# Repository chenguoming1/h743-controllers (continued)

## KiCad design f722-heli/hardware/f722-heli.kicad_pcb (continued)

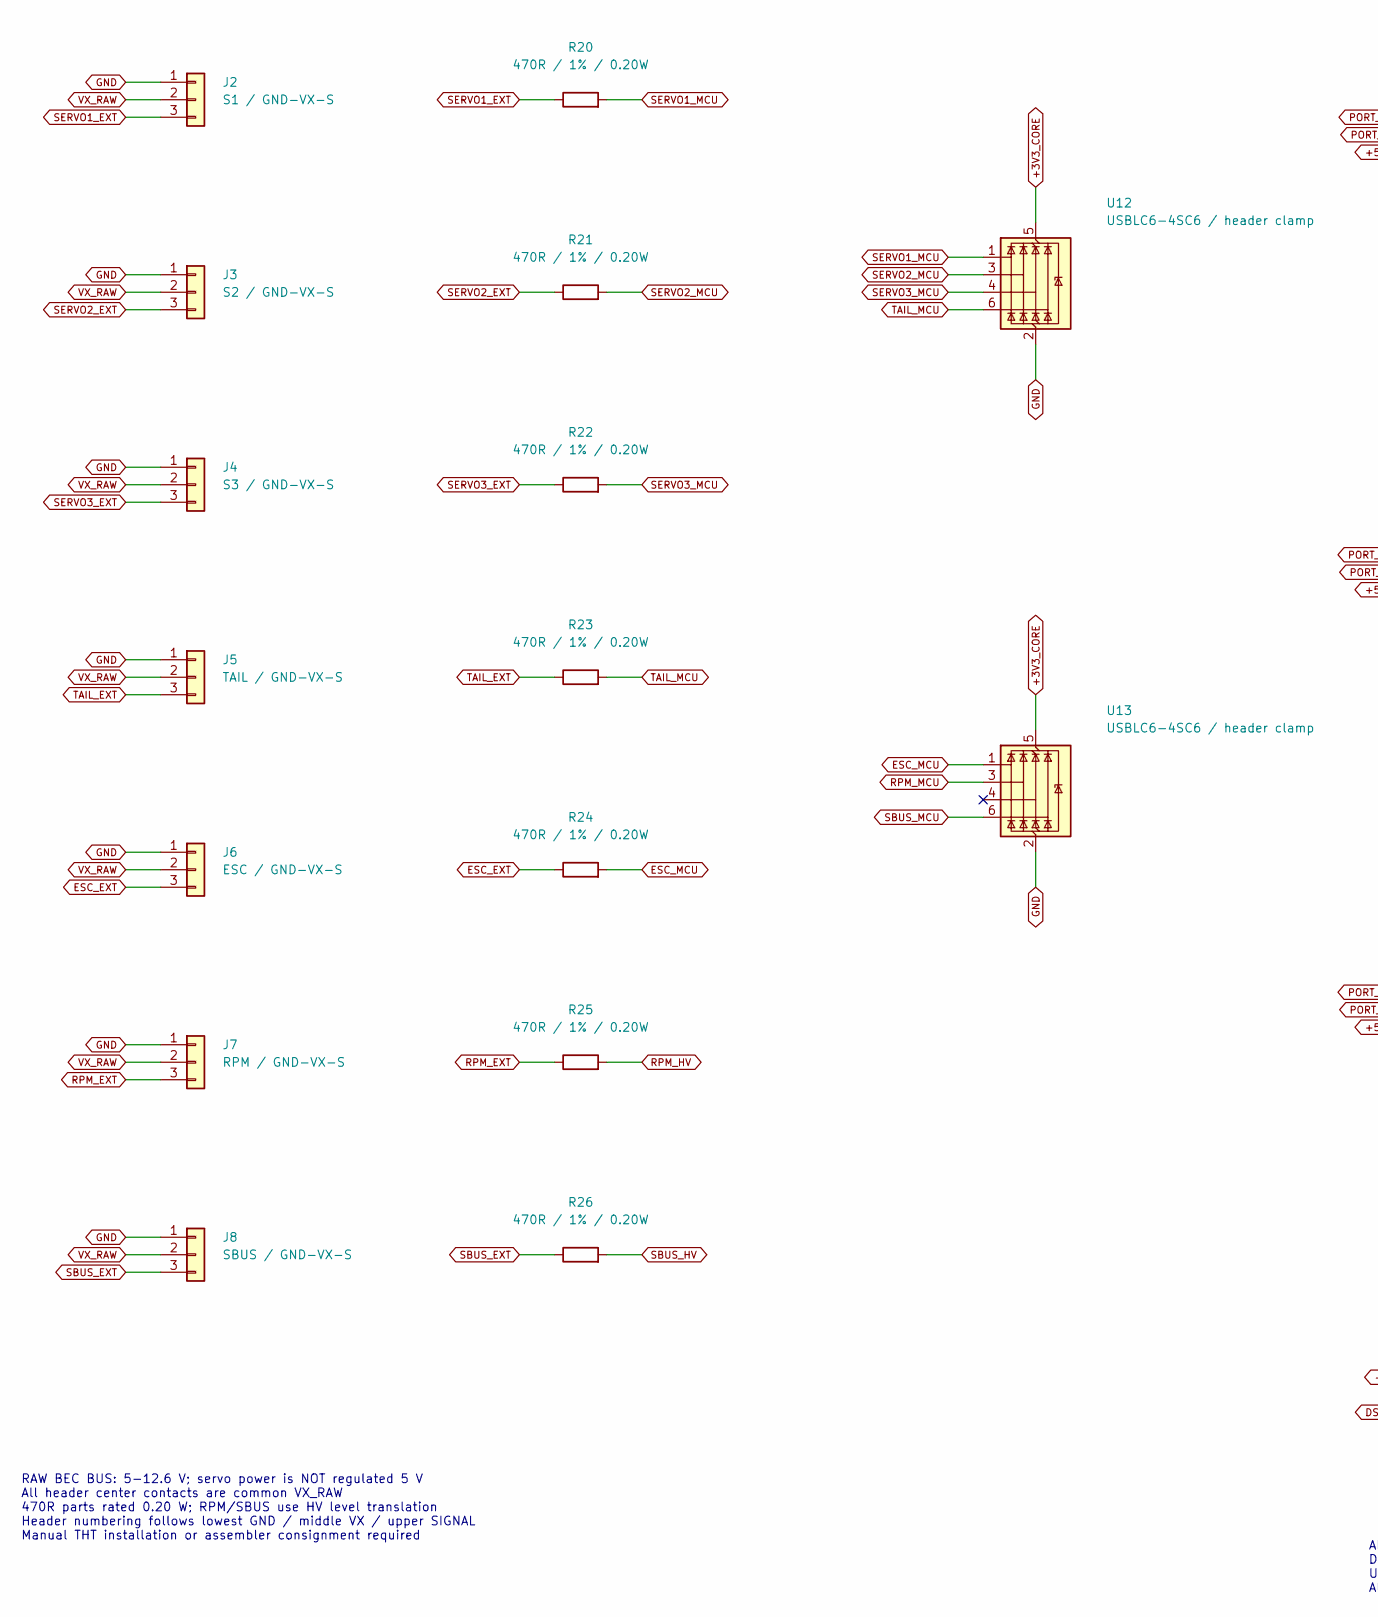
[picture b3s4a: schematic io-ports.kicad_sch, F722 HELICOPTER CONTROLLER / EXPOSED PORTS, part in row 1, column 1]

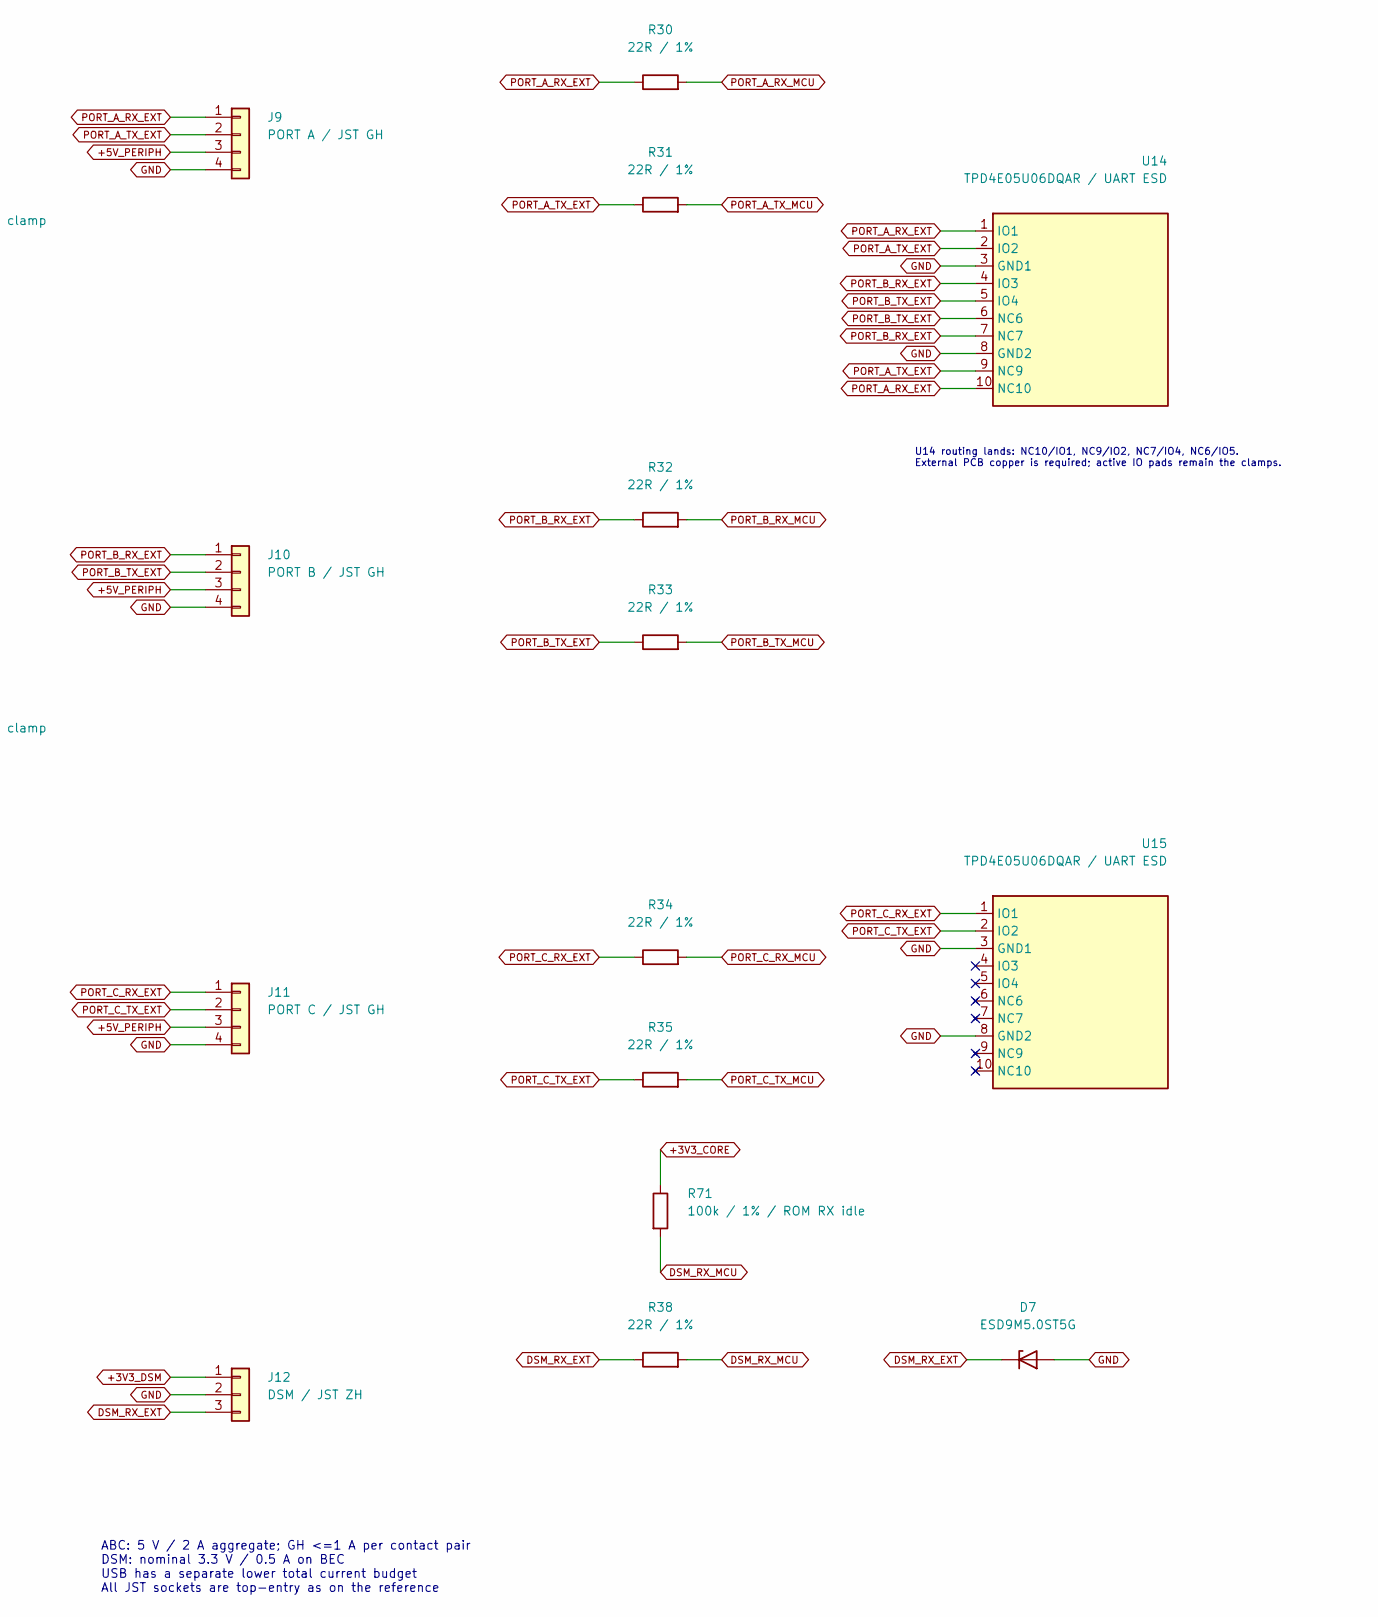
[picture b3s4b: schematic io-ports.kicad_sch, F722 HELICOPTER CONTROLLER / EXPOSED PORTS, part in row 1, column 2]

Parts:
D7: ESD9M5.0ST5G; D_SOD-923; MPN ESD9M5.0ST5G; LCSC C242267
J2: S1 / GND-VX-S; Samtec_HTSW-101-08-L-T-RA_TripleRow_OpenEdgeSilk; MPN HTSW-101-08-L-T-RA
J3: S2 / GND-VX-S; Samtec_HTSW-101-08-L-T-RA_TripleRow_OpenEdgeSilk; MPN HTSW-101-08-L-T-RA
J4: S3 / GND-VX-S; Samtec_HTSW-101-08-L-T-RA_TripleRow_OpenEdgeSilk; MPN HTSW-101-08-L-T-RA
J5: TAIL / GND-VX-S; Samtec_HTSW-101-08-L-T-RA_TripleRow_OpenEdgeSilk; MPN HTSW-101-08-L-T-RA
J6: ESC / GND-VX-S; Samtec_HTSW-101-08-L-T-RA_TripleRow_OpenEdgeSilk; MPN HTSW-101-08-L-T-RA
J7: RPM / GND-VX-S; Samtec_HTSW-101-08-L-T-RA_TripleRow_OpenEdgeSilk; MPN HTSW-101-08-L-T-RA
J8: SBUS / GND-VX-S; Samtec_HTSW-101-08-L-T-RA_TripleRow_OpenEdgeSilk; MPN HTSW-101-08-L-T-RA
J9: PORT A / JST GH; JST_GH_BM04B-GHS-TBT_1x04-1MP_P1.25mm_Vertical; MPN BM04B-GHS-TBT(LF)(SN); LCSC C161692
J10: PORT B / JST GH; JST_GH_BM04B-GHS-TBT_1x04-1MP_P1.25mm_Vertical; MPN BM04B-GHS-TBT(LF)(SN); LCSC C161692
J11: PORT C / JST GH; JST_GH_BM04B-GHS-TBT_1x04-1MP_P1.25mm_Vertical; MPN BM04B-GHS-TBT(LF)(SN); LCSC C161692
J12: DSM / JST ZH; JST_ZH_B3B-ZR-SM4-TF_1x03-1MP_P1.50mm_Vertical; MPN B3B-ZR-SM4-TF(LF)(SN); LCSC C489717
R20, R21, R22, R23, R24, R25, R26: 470R / 1% / 0.20W; Panasonic_ERJPA2_0402; MPN ERJPA2F4700X; LCSC C427238
R30, R32, R33, R34, R35, R38: 22R / 1%; R_0402_1005Metric; MPN 0402WGF220JTCE; LCSC C25092
R31: 22R / 1%; R_0201_0603Metric_YAGEO_AC; MPN AC0201FR-0722RL; LCSC C144830
R71: 100k / 1% / ROM RX idle; R_0402_1005Metric; MPN 0402WGF1003TCE; LCSC C25741
U12, U13: USBLC6-4SC6 / header clamp; SOT-23-6; MPN USBLC6-4SC6; LCSC C111212
U14, U15: TPD4E05U06DQAR / UART ESD; Texas_DQA0010B_TPD4E05U06_2.5x1mm; MPN TPD4E05U06DQAR; LCSC C138714

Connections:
+3V3_CORE: R71.1, U12.5 (VBUS), U13.5 (VBUS); also elsewhere on the board
+3V3_DSM: J12.1; also elsewhere on the board
+5V_PERIPH: J9.3, J10.3, J11.3; also elsewhere on the board
DSM_RX_EXT: D7.1 (K), J12.3, R38.1
DSM_RX_MCU: R38.2, R71.2; also elsewhere on the board
ESC_EXT: J6.3, R24.1
GND: D7.2 (A), J2.1, J3.1, J4.1, J5.1, J6.1, J7.1, J8.1, J9.4, J10.4, J11.4, J12.2, U12.2 (GND), U13.2 (GND), U14.3 (GND1), U14.8 (GND2), U15.3 (GND1), U15.8 (GND2); also elsewhere on the board
PORT_A_RX_EXT: J9.1, R30.1, U14.1 (IO1), U14.10 (NC10)
PORT_A_RX_MCU: R30.2; also elsewhere on the board
PORT_A_TX_EXT: J9.2, R31.1, U14.2 (IO2), U14.9 (NC9)
PORT_A_TX_MCU: R31.2; also elsewhere on the board
PORT_B_RX_EXT: J10.1, R32.1, U14.4 (IO3), U14.7 (NC7)
PORT_B_RX_MCU: R32.2; also elsewhere on the board
PORT_B_TX_EXT: J10.2, R33.1, U14.5 (IO4), U14.6 (NC6)
PORT_B_TX_MCU: R33.2; also elsewhere on the board
PORT_C_RX_EXT: J11.1, R34.1, U15.1 (IO1), U15.10 (NC10)
PORT_C_RX_MCU: R34.2; also elsewhere on the board
PORT_C_TX_EXT: J11.2, R35.1, U15.2 (IO2), U15.9 (NC9)
PORT_C_TX_MCU: R35.2; also elsewhere on the board
RPM_EXT: J7.3, R25.1
RPM_HV: R25.2; also elsewhere on the board
SBUS_EXT: J8.3, R26.1
SBUS_HV: R26.2; also elsewhere on the board
SERVO1_EXT: J2.3, R20.1
SERVO1_MCU: R20.2, U12.1 (I/O1); also elsewhere on the board
SERVO2_EXT: J3.3, R21.1
SERVO2_MCU: R21.2, U12.3 (I/O2); also elsewhere on the board
SERVO3_EXT: J4.3, R22.1
SERVO3_MCU: R22.2, U12.4 (I/O3); also elsewhere on the board
TAIL_EXT: J5.3, R23.1
TAIL_MCU: R23.2, U12.6 (I/O4); also elsewhere on the board
VX_RAW: J2.2, J3.2, J4.2, J5.2, J6.2, J7.2, J8.2; also elsewhere on the board

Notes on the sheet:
RAW BEC BUS: 5-12.6 V; servo power is NOT regulated 5 V All header center contacts are common VX_RAW 470R parts rated 0.20 W; RPM/SBUS use HV level translation Header numbering follows lowest GND / middle VX / upper SIGNAL Manual THT installation or assembler consignment required
ABC: 5 V / 2 A aggregate; GH <=1 A per contact pair DSM: nominal 3.3 V / 0.5 A on BEC USB has a separate lower total current budget All JST sockets are top-entry as on the reference
U14 routing lands: NC10/IO1, NC9/IO2, NC7/IO4, NC6/IO5. External PCB copper is required; active IO pads remain the clamps.

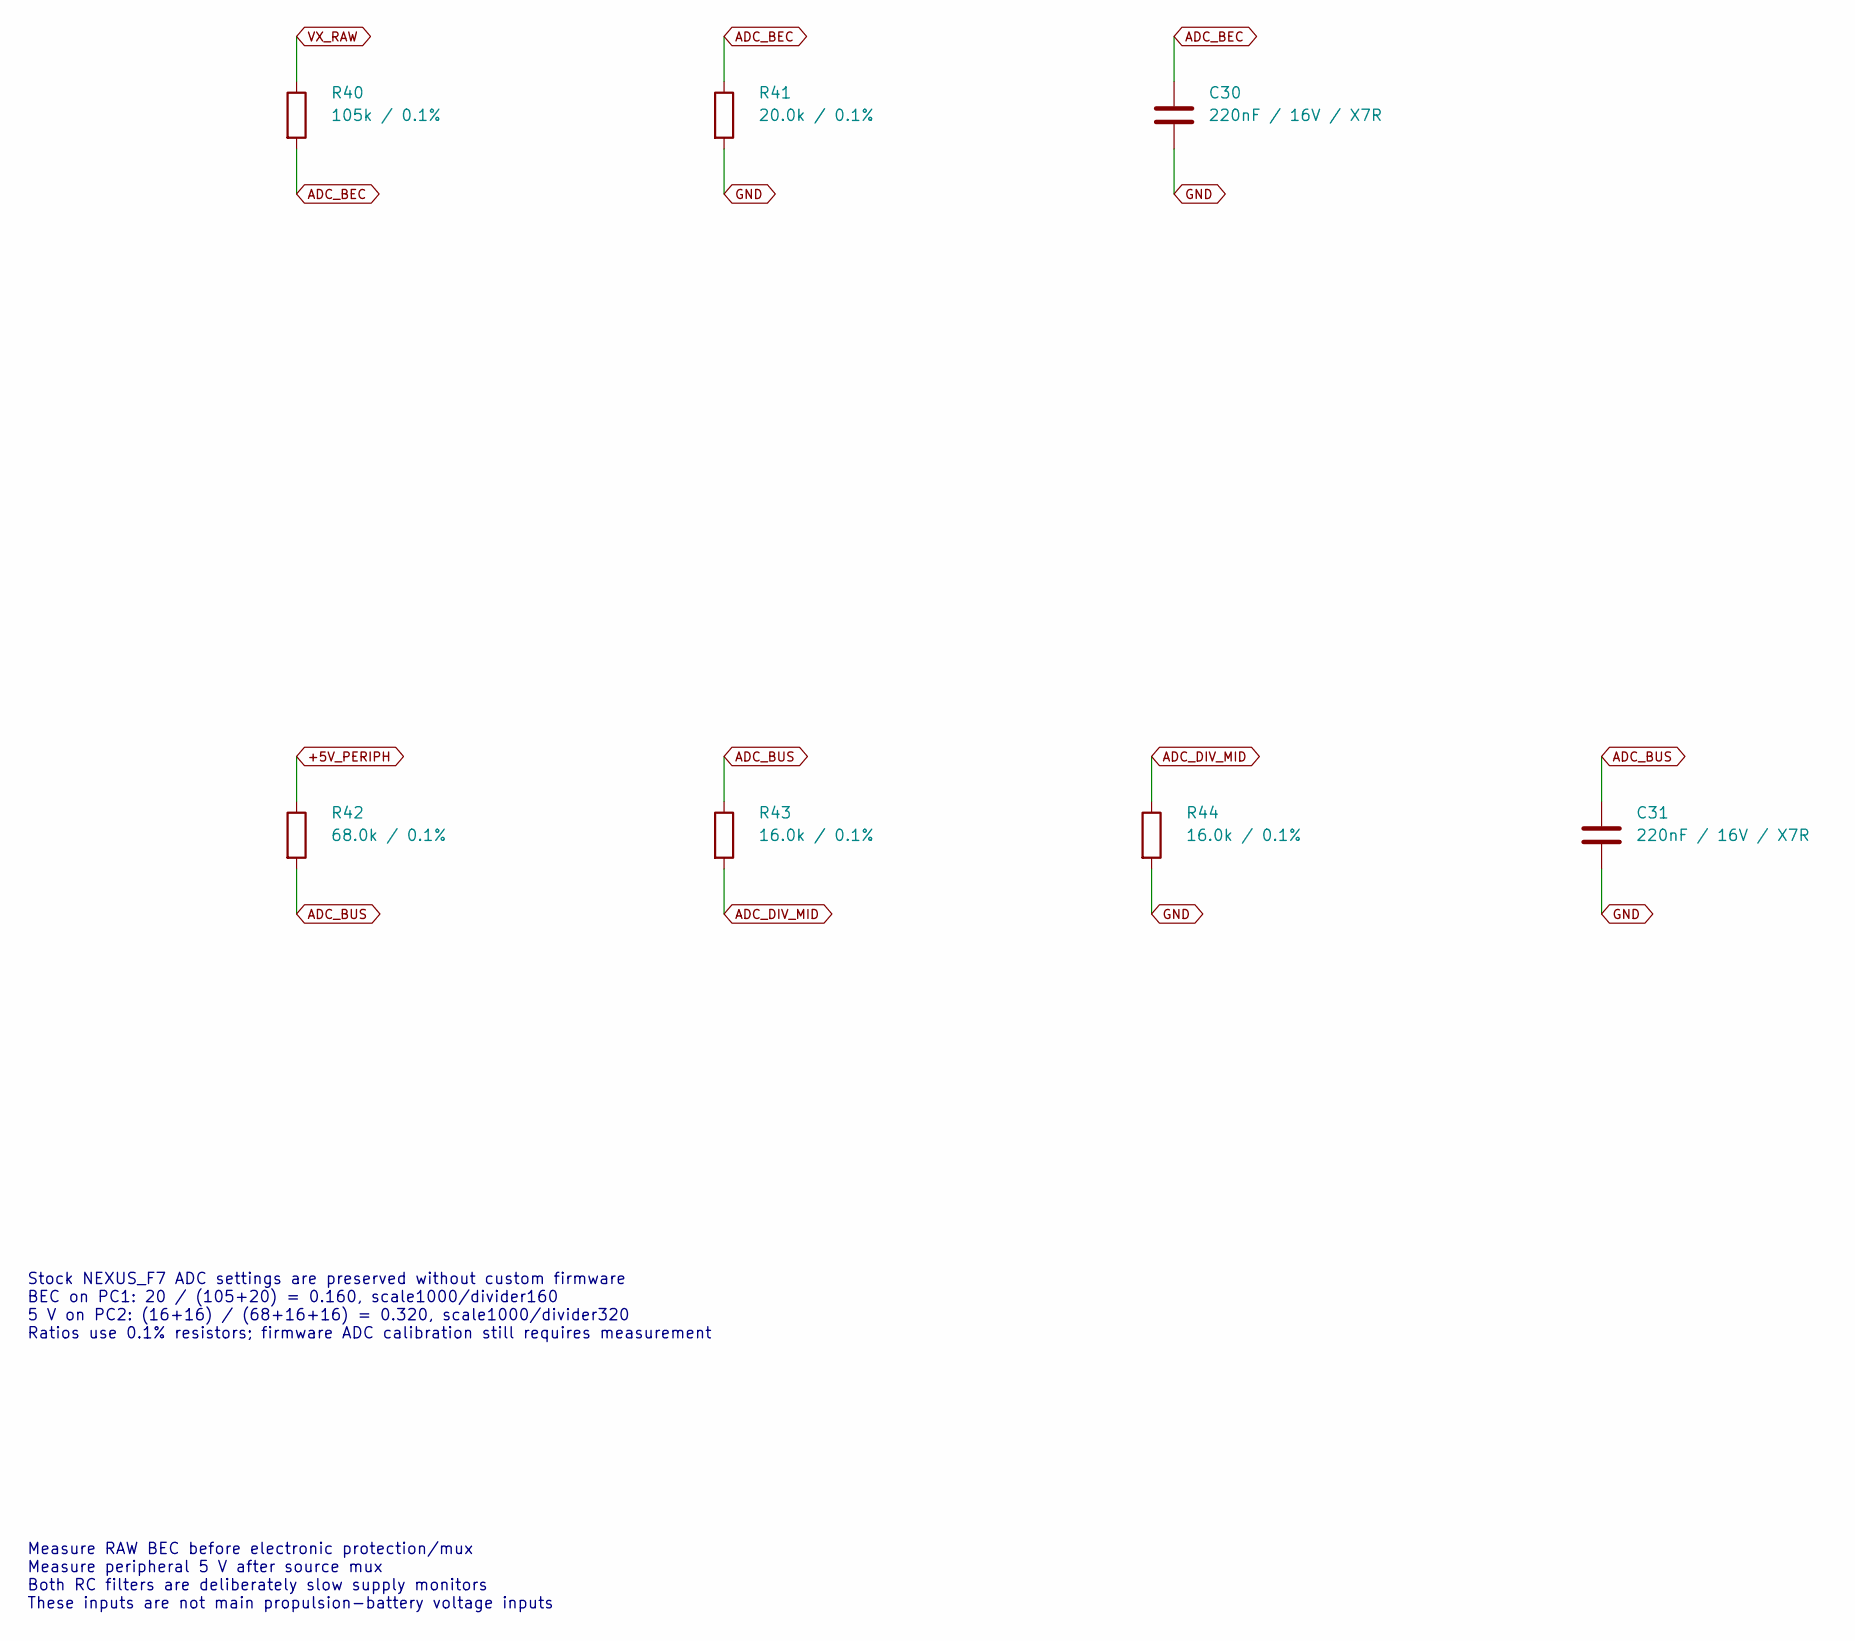
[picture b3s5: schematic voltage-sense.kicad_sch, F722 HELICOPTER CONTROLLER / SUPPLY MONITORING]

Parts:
C30, C31: 220nF / 16V / X7R; C_0402_1005Metric; MPN CL05B224KO5NNNC; LCSC C16772
R40: 105k / 0.1%; R_0402_1005Metric; MPN ARG02BTC1053; LCSC C2984407
R41: 20.0k / 0.1%; R_0402_1005Metric; MPN RT0402BRD0720KL; LCSC C705630
R42: 68.0k / 0.1%; R_0402_1005Metric; MPN ARG02BTC6802; LCSC C5266108
R43, R44: 16.0k / 0.1%; R_0402_1005Metric; MPN RT0402BRD0716KL; LCSC C513647

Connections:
+5V_PERIPH: R42.1; also elsewhere on the board
ADC_BEC: C30.1, R40.2, R41.1; also elsewhere on the board
ADC_BUS: C31.1, R42.2, R43.1; also elsewhere on the board
ADC_DIV_MID: R43.2, R44.1
GND: C30.2, C31.2, R41.2, R44.2; also elsewhere on the board
VX_RAW: R40.1; also elsewhere on the board

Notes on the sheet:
Stock NEXUS_F7 ADC settings are preserved without custom firmware BEC on PC1: 20 / (105+20) = 0.160, scale1000/divider160 5 V on PC2: (16+16) / (68+16+16) = 0.320, scale1000/divider320 Ratios use 0.1% resistors; firmware ADC calibration still requires measurement
Measure RAW BEC before electronic protection/mux Measure peripheral 5 V after source mux Both RC filters are deliberately slow supply monitors These inputs are not main propulsion-battery voltage inputs

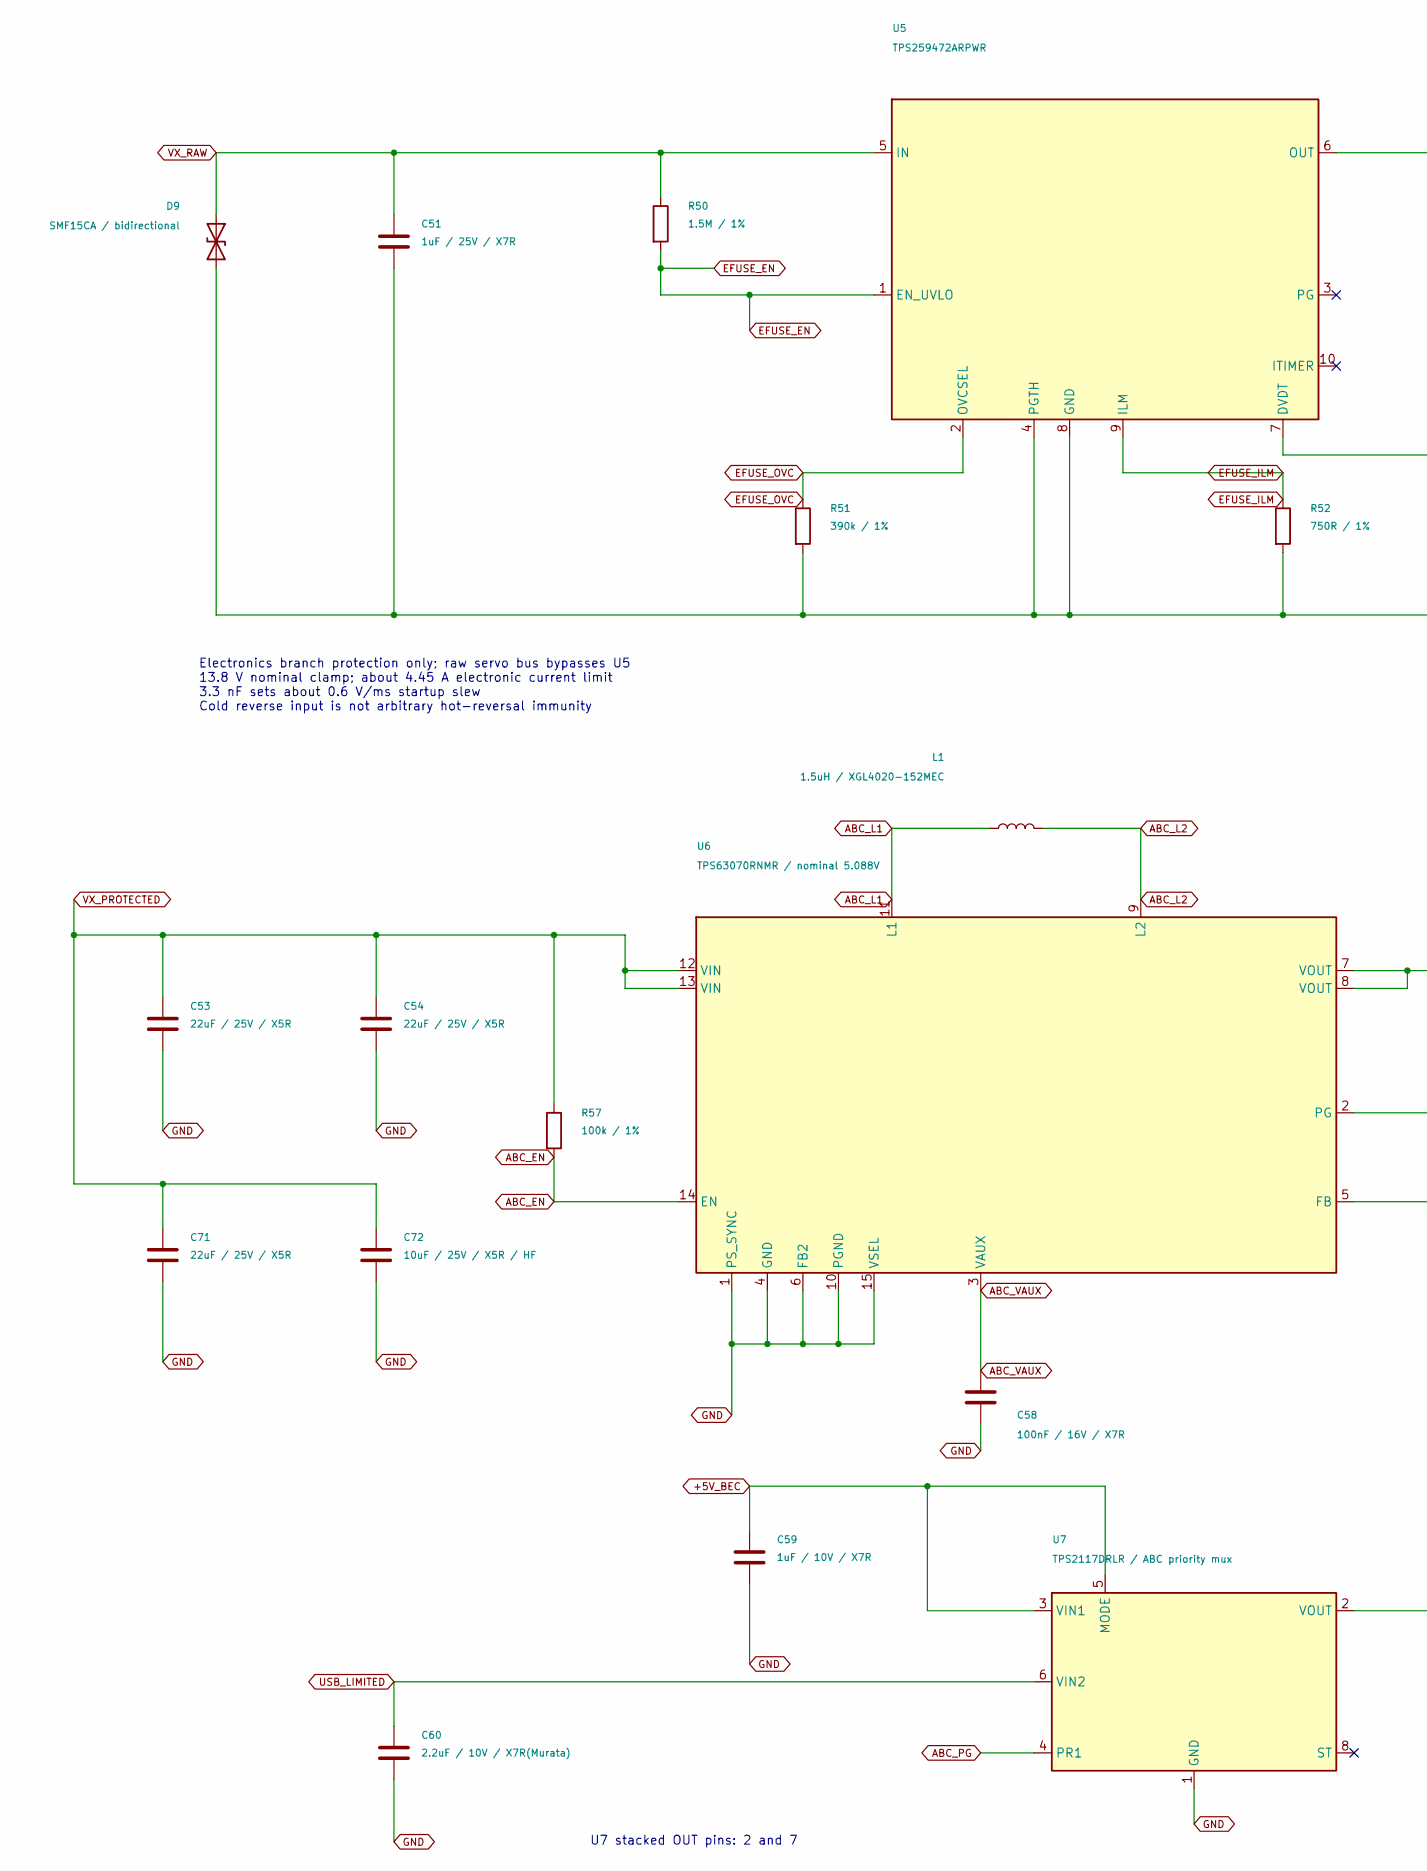
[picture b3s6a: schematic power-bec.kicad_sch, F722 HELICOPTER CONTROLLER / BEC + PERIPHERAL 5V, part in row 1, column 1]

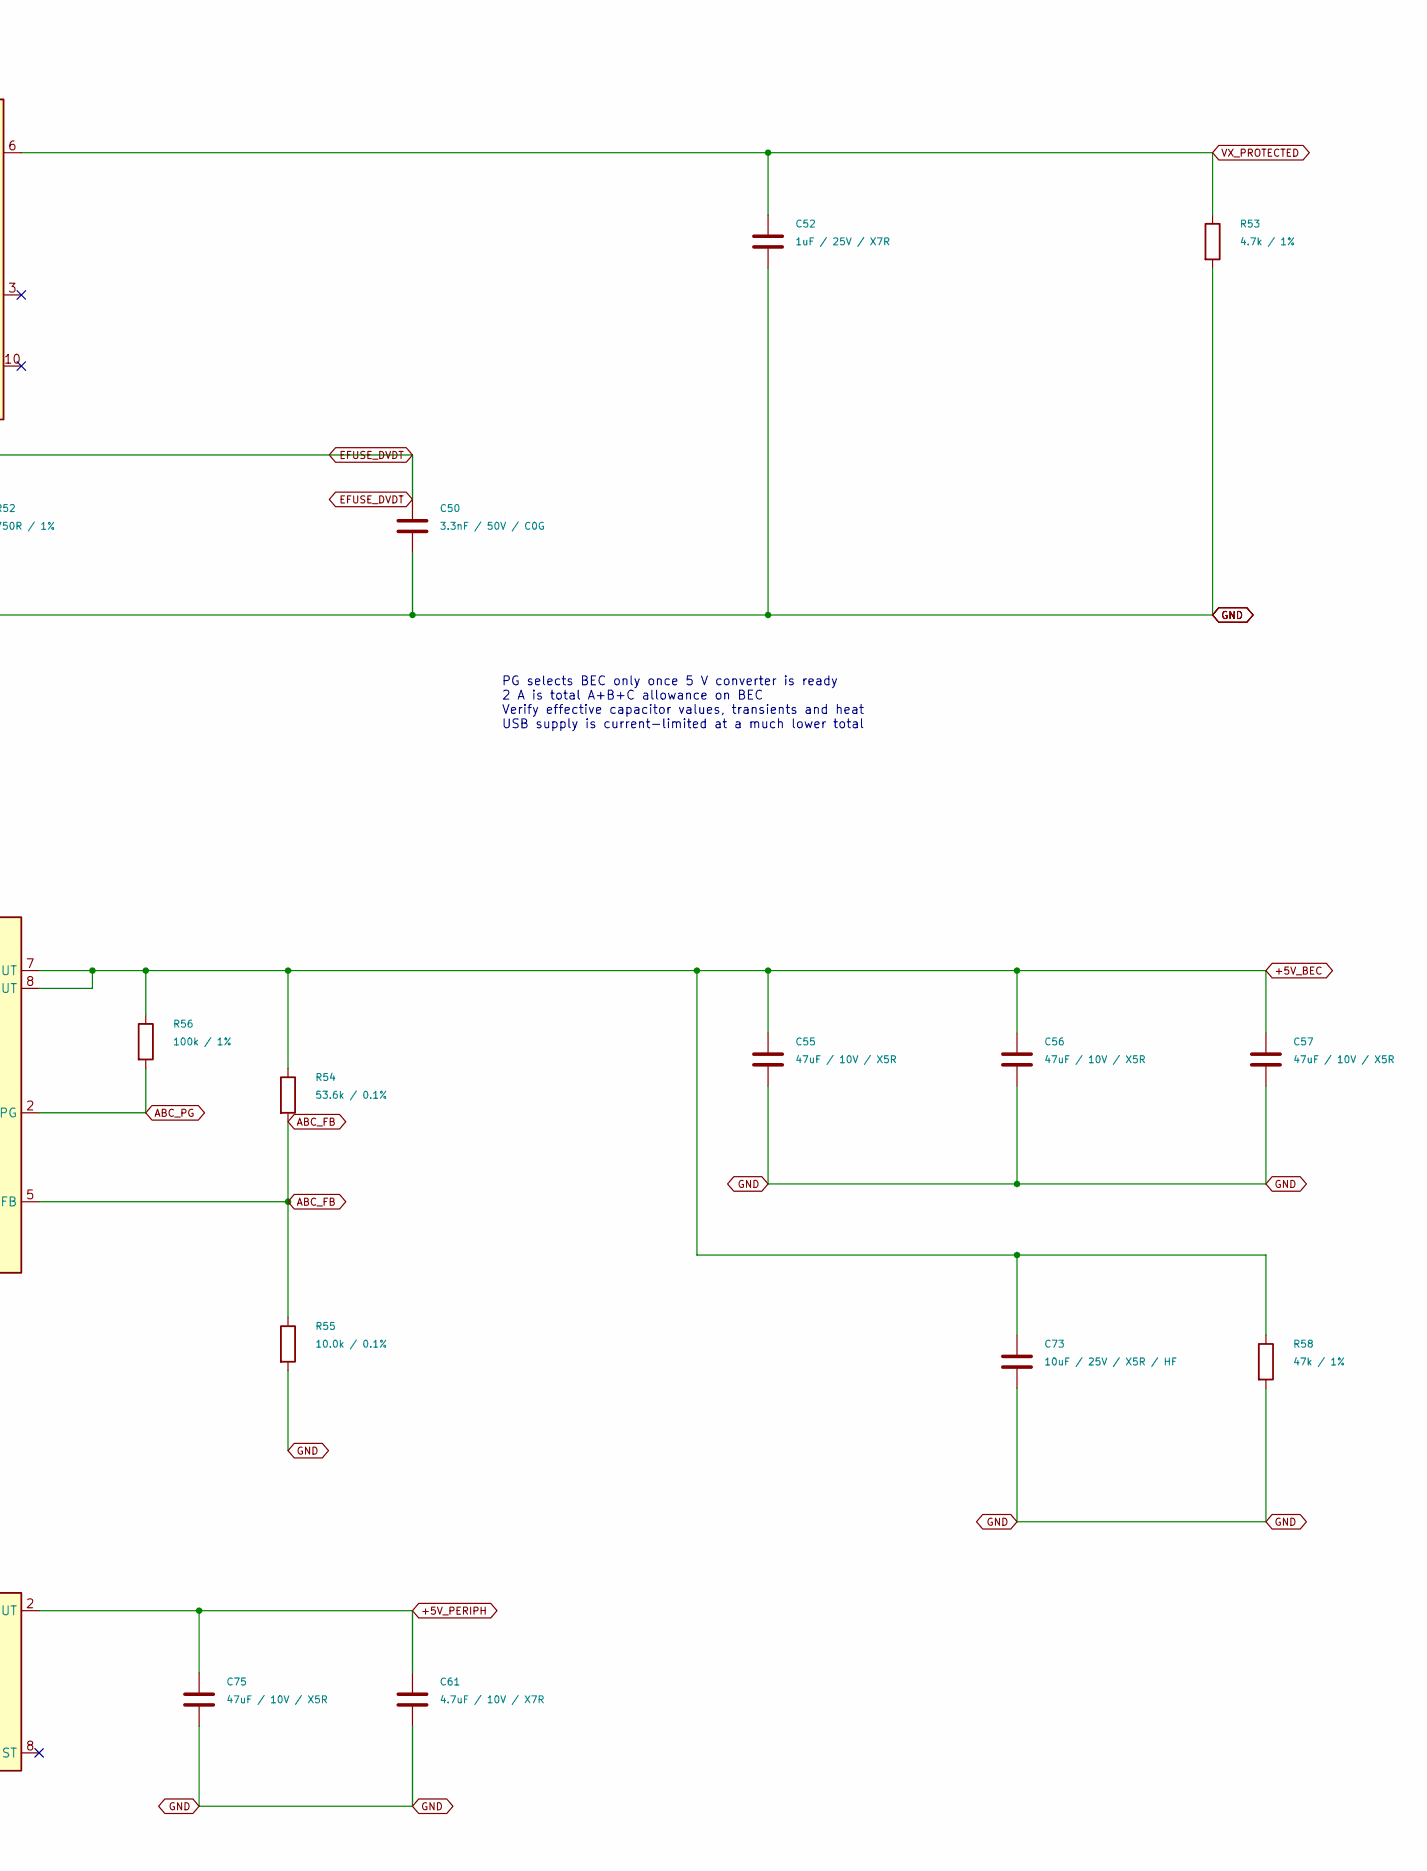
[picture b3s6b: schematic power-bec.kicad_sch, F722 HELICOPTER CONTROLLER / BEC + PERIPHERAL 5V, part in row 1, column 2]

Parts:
C50: 3.3nF / 50V / C0G; C_0402_1005Metric; MPN GRM1555C1H332JE01D; LCSC C1518207
C51, C52: 1uF / 25V / X7R; C_0603_1608Metric; MPN CL10B105KA8NNNC; LCSC C29936
C53, C54, C71: 22uF / 25V / X5R; C_0805_2012Metric; MPN GRM21BR61E226ME44L; LCSC C86816
C55, C56, C57, C75: 47uF / 10V / X5R; C_0805_2012Metric; MPN GRM21BR61A476ME15L; LCSC C124129
C58: 100nF / 16V / X7R; C_0402_1005Metric; MPN CL05B104KO5NNNC; LCSC C1525
C59: 1uF / 10V / X7R; C_0603_1608Metric; MPN CL10B105KP8NNNC; LCSC C95843
C60: 2.2uF / 10V / X7R(Murata); Murata_GRM155Z71A225KE44_0402; MPN GRM155Z71A225KE44D; LCSC C2999759
C61: 4.7uF / 10V / X7R; C_0603_1608Metric; MPN GRM188Z71A475KE15D; LCSC C913474
C72, C73: 10uF / 25V / X5R / HF; C_0603_1608Metric; MPN TMK107BBJ106MA-T; LCSC C386081
D9: SMF15CA / bidirectional; Littelfuse_SMF_SOD123FL; MPN SMF15CA; LCSC C1851361
L1: 1.5uH / XGL4020-152MEC; Coilcraft_XGL4020; MPN XGL4020-152MEC; LCSC C7417180
R50: 1.5M / 1%; R_0402_1005Metric; MPN 0402WGF1504TCE; LCSC C22276
R51: 390k / 1%; R_0402_1005Metric; MPN 0402WGF3903TCE; LCSC C25782
R52: 750R / 1%; R_0402_1005Metric; MPN 0402WGF7500TCE; LCSC C25132
R53: 4.7k / 1%; Panasonic_ERJPA2_0402; MPN ERJPA2F4701X; LCSC C427244
R54: 53.6k / 0.1%; R_0402_1005Metric; MPN RT0402BRD0753K6L; LCSC C852835
R55: 10.0k / 0.1%; R_0402_1005Metric; MPN RT0402BRD0710KL; LCSC C190095
R56, R57: 100k / 1%; R_0402_1005Metric; MPN 0402WGF1003TCE; LCSC C25741
R58: 47k / 1%; R_0402_1005Metric; MPN 0402WGF4702TCE; LCSC C25792
U5: TPS259472ARPWR; Texas_RPW0010A_TPS259472_2x2mm; MPN TPS259472ARPWR; LCSC C3662789
U6: TPS63070RNMR / nominal 5.088V; Texas_RNM0015A_TPS63070_2.5x3mm; MPN TPS63070RNMR; LCSC C109322
U7: TPS2117DRLR / ABC priority mux; SOT-583-8; MPN TPS2117DRLR; LCSC C22399676

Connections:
+5V_BEC: C55.1, C56.1, C57.1, C59.1, C73.1, R54.1, R56.1, R58.1, U6.7 (VOUT), U6.8 (VOUT), U7.3 (VIN1), U7.5 (MODE)
+5V_PERIPH: C61.1, C75.1, U7.2 (VOUT), U7.7 (VOUT); also elsewhere on the board
ABC_EN: R57.2, U6.14 (EN)
ABC_FB: R54.2, R55.1, U6.5 (FB)
ABC_L1: L1.1, U6.11 (L1)
ABC_L2: L1.2, U6.9 (L2)
ABC_PG: R56.2, U6.2 (PG), U7.4 (PR1)
ABC_VAUX: C58.1, U6.3 (VAUX)
EFUSE_DVDT: C50.1, U5.7 (DVDT)
EFUSE_EN: R50.2, U5.1 (EN_UVLO)
EFUSE_ILM: R52.1, U5.9 (ILM)
EFUSE_OVC: R51.1, U5.2 (OVCSEL)
GND: C50.2, C51.2, C52.2, C53.2, C54.2, C55.2, C56.2, C57.2, C58.2, C59.2, C60.2, C61.2, C71.2, C72.2, C73.2, C75.2, D9.2 (A2), R51.2, R52.2, R53.2, R55.2, R58.2, U5.4 (PGTH), U5.8 (GND), U6.1 (PS_SYNC), U6.4 (GND), U6.6 (FB2), U6.10 (PGND), U6.15 (VSEL), U7.1 (GND); also elsewhere on the board
USB_LIMITED: C60.1, U7.6 (VIN2); also elsewhere on the board
VX_PROTECTED: C52.1, C53.1, C54.1, C71.1, C72.1, R53.1, R57.1, U5.6 (OUT), U6.12 (VIN), U6.13 (VIN); also elsewhere on the board
VX_RAW: C51.1, D9.1 (A1), R50.1, U5.5 (IN); also elsewhere on the board

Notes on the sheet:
Electronics branch protection only; raw servo bus bypasses U5 13.8 V nominal clamp; about 4.45 A electronic current limit 3.3 nF sets about 0.6 V/ms startup slew Cold reverse input is not arbitrary hot-reversal immunity
PG selects BEC only once 5 V converter is ready 2 A is total A+B+C allowance on BEC Verify effective capacitor values, transients and heat USB supply is current-limited at a much lower total
U7 stacked OUT pins: 2 and 7

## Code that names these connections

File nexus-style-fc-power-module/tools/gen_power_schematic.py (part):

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        s.power(G, x, 64.77, "down")
    s.part("C23", 114.3, 81.28)
    s.wire(u["9"], (114.3, u["9"][1]))
    s.label("SS_5V", 115.57, u["9"][1])
    s.power(G, 114.3, 85.09, "down")
    s.wire(u["8"], (119.38, u["8"][1]), (119.38, 97.79))
    s.wire(u["7"], (119.38, u["7"][1]))
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    s.wire((160.02, u["3"][1]), (160.02, u["1"][1]))
    s.part("L1", 170.18, 62.23, rot=90, text="above")
    s.wire((160.02, u["1"][1]), s.pin("L1", "1"))
    s.label("SW_5V", 160.02, 62.23)
    s.wire(s.pin("L1", "2"), (199.39, 62.23))         # 5V_BUCK node
    s.label("5V_BUCK", 199.39, 62.23)
    s.wire(u["14"], (176.53, u["14"][1]), (176.53, 62.23))   # VOS senses the output
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    s.wire(s.pin("R11", "2"), s.pin("R12", "1"))
    s.power(G, 194.31, 81.28, "down")
    s.wire(u["5"], (189.23, u["5"][1]), (189.23, 71.12), (194.31, 71.12))
    s.label("FB_5V", 163.83, u["5"][1])
    for n in ("17", "6", "15", "16"):                  # EP, AGND, PGND
        s.wire(u[n], (160.02, u[n][1]))
    s.wire((160.02, u["17"][1]), (160.02, 97.79))
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    s.part("R14", 243.84, 91.44, text="left")
    s.wire(s.pin("R13", "2"), s.pin("R14", "1"))
    s.wire(m["4"], (254.0, m["4"][1]), (254.0, 87.63), (243.84, 87.63))
    s.label("PR1", 255.27, m["4"][1])
    s.power(G, 243.84, 95.25, "down")
    s.wire(m["7"], (297.18, m["7"][1]), (297.18, 63.5), (325.12, 63.5))     # VOUT -> 5V bus
    s.power("5V", 304.8, 63.5)
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    s.power("VBUS", 30.48, 166.37)
    s.wire(s.pin("D5", "1"), (50.8, 156.21), (50.8, 166.37))
    k = s.part("U14", 114.3, 165.1, mirror=True, text="ic")
    s.wire(s.pin("D6", "1"), k["6"])                  # VSYS -> VIN
    s.power("VSYS", 55.88, 166.37)
    s.flag(63.5, 166.37, "down")
    s.part("C27", 71.12, 170.18)
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    s.wire(k["7"], (88.9, k["7"][1]), (88.9, k["6"][1]))   # EN tied to VIN
    s.part("R15", 83.82, k["8"][1], rot=270, text="top")        # pin 1 on S-CONF, pin 2 to GND
    s.wire(s.pin("R15", "1"), k["8"])
    s.label("SCONF", 87.63, k["8"][1])
    s.wire(s.pin("R15", "2"), (76.2, k["8"][1]))
    s.power(G, 76.2, k["8"][1], "left")
    s.wire(k["5"], (91.44, k["5"][1]), (91.44, 176.53))
    s.power(G, 91.44, 176.53, "down")
    s.part("L2", 147.32, k["4"][1], rot=90, text="above")
    s.wire(k["4"], s.pin("L2", "1"))
    s.label("SW_3V3", 135.89, k["4"][1])
    s.wire(s.pin("L2", "2"), (177.8, k["4"][1]))
    s.wire(k["3"], (137.16, k["3"][1]), (137.16, 156.21), (157.48, 156.21), (157.48, k["4"][1]))   # VOS
    s.part("C28", 162.56, 172.72)
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
    # ---------------------------------------------------------------- ADC sense dividers
    s.box(dp.GROUP_TITLES["SENSE"], 200.66, 172.72, 340.36, 236.22)
    for top, r1, r2, c, x, net, note in (("VX", "R16", "R17", "C29", 210.82, "VX_SENSE", "-> MCU PC0"),
                                         ("5V", "R18", "R19", "C30", 266.7, "5V_SENSE", "-> MCU PC1")):
        s.power(top, x, 190.5)
        s.part(r1, x, 198.12)
        s.wire((x, 190.5), s.pin(r1, "1"))
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    j = s.part("J6", 68.58, 228.6, text="ictop")
    for side, sx_, d in (("A", -1, "left"), ("B", 1, "right")):
        x0 = j[side + "1"][0] + sx_ * 5.08                   # stub ends
        for pin, net in (("1", G), ("4", "VBUS_C"), ("6", "USB_DP"), ("7", "USB_DM"), ("9", "VBUS_C"), ("12", G)):
            pt = j[side + pin]
            s.wire(pt, (x0, pt[1]))
            if net == G:
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    s.power(G, j["EP"][0], j["EP"][1] + 2.54, "down")
    f1 = s.part("F1", 127.0, 219.71, text="above")         # VBUS_C -> fuse -> VBUS
    s.wire((114.3, f1["1"][1]), f1["1"])
    s.label("VBUS_C", 114.3, f1["1"][1], "left")
    s.wire(f1["2"], (153.67, f1["2"][1]))
    s.power("VBUS", 140.97, f1["2"][1])
    s.flag(153.67, f1["2"][1])
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    s.label("USB_DM", 138.43, 226.06, "left", glob=True)
    s.wire(e["3"], (143.51, e["3"][1]), (143.51, 256.54), (181.61, 256.54), (181.61, e["4"][1]), e["4"])
    s.wire((143.51, 256.54), (138.43, 256.54))
    s.label("USB_DP", 138.43, 256.54, "left", glob=True)
    s.wire(e["2"], (140.97, e["2"][1]))
    s.power(G, 140.97, e["2"][1], "left")
    s.wire(e["5"], (184.15, e["5"][1]))
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
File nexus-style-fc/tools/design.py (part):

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C("1uF", "3V3", "GND", ("near", "U1", "13", "B"), "MCU", note="VDDA")
C("100nF", "3V3", "GND", ("near", "U1", "13", "B"), "MCU", note="VDDA")
C("100nF", "3V3", "GND", ("near", "U1", "1", "B"), "MCU", note="VBAT")
C("4.7uF", "VCAP", "GND", ("near", "U1", "30", "F"), "MCU", fp=C0603, note="VCAP_1 (LQFP64: single 4.7uF), top side over the pin")
C("100nF", "NRST", "GND", ("near", "U1", "7", "B"), "MCU", note="NRST")
R("10k", "BOOT0", "GND", ("near", "U1", "60", "B"), "MCU", note="BOOT0 pull-down")
part("Y1", "NexusFC:32258M20PF10PPM", "8MHz 20pF", "NexusFC:CRYSTAL-SMD_4P-L3.2-W2.5-BL", "C5181477",
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part("TP5", "Connector:TestPoint", "NRST", "TestPoint:TestPoint_Pad_D1.0mm", "", {"1": "NRST"},
     ("xy", 1.3, 26.6, 0, "B"), "MCU", "SWD")

# LEDs: PC14/PC15 sit behind the backup-domain switch -> sink only, <= 3 mA
part("D1", "NexusFC:XL-1608SYGC-04", "LED1 yellow-green", "NexusFC:LED0603-RD_GREEN", "C965806",
     {"2": "LED1_A", "1": "LED1_K"}, ("xy", 8.6, 24.2, 0, "F"), "LED", "PC14, active-low")
R("1k", "3V3", "LED1_A", ("near", "D1", "2", "F"), "LED", note="~1.3 mA")
part("D2", "NexusFC:XL-1608SURC-06", "LED2 red", "NexusFC:LED0603-RD_RED", "C965799",
     {"2": "LED2_A", "1": "LED2_K"}, ("xy", 13.8, 24.2, 0, "F"), "LED", "PC15, active-low")
R("1k", "3V3", "LED2_A", ("near", "D2", "2", "F"), "LED", note="~1.3 mA")
part("D3", "NexusFC:XL-1608UBC-04", "Power LED blue", "NexusFC:LED0603-RD_BLUE", "C965807",
     {"2": "LED3_A", "1": "GND"}, ("xy", 11.2, 24.2, 0, "F"), "LED", "5 V bus present")
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    "D5": ("near", "U14", "6", "B"),
    "D6": ("near", "F1", "2", "B"),
    # SWD / debug pads on the top side, beside the USB socket and the BOOT button (under the cover)
    # SWD pads on the right, the side of the MCU's PA13/PA14; 3V3 / GND / NRST on the left
    "TP1": ("xy", 21.15, 26.2, 0, "F"), "TP2": ("xy", 21.15, 28.4, 0, "F"), "TP5": ("xy", 1.6, 30.4, 0, "F"),
    "TP3": ("xy", 1.6, 26.0, 0, "F"), "TP4": ("xy", 1.6, 28.2, 0, "F"),
}
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    if p["ref"].startswith("TP"):
        return (9, 0)
    anchor = p["place"][1]
    if p["note"].startswith(("VCAP", "VDD pin", "crystal load", "VDDA")):
        return (0, 0)                              # MCU-critical decoupling goes first of all
    tier = 0 if anchor in _REG | {"Y1"} or p["ref"] in ("D5",) \
        else 1 if anchor == "U1" else 2
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    # C5 remains the original 0603 bulk capacitor on 3V3.
    by_ref["C9"].update(
        fp="NexusFC:C_0402_1005Metric__VCAP_Dense", lcsc="C368809",
        pins={"1": "VCAP_C", "2": "GND"},
        note="VCAP1: Samsung CL05A475KP5NRNC, 4.7uF +/-10%, 10V X5R; 120mOhm series R23")
    selected.append(dict(
        ref="R23", sym="Device:R", value="0.12",
        fp="NexusFC:R_0402_1005Metric__VCAP_Dense", lcsc="C2766886",
        pins={"1": "VCAP", "2": "VCAP_C"}, group="MCU",
        note="VCAP1 damping: 120 mOhm +/-5%, 0402WGJ012KTCE; C9 branch only; retain 4.7uF"))
    by_ref["D4"].update(sym="NexusReviewed:SMF9_0A_C1973343", value="SMF9.0A",
        fp="NexusFC:SOD-123FL_L2.8-W1.8-LS3.6-RD__Littelfuse_SMF9", lcsc="C1973343",
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    u10 = by_ref["U10"]
    assert (u10["value"], u10["lcsc"], u10["fp"]) == (
        "TPS70933DBVR", "C89347", "NexusFC:SOT-23-5_L3.0-W1.7-P0.95-LS2.8-BL")
    assert u10["pins"] == {"1": "VSYS", "2": "GND", "3": None, "4": None, "5": "3V3_SENS"}
    u10["fp"] = "NexusFC:TPS70933DBVR_TI_DBV0005A"
    assert set(MAIN_ROUTED_PLACEMENT) == {p["ref"] for p in selected}, "Main placement coverage changed"
    for p in selected:
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
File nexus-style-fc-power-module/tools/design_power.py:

"""Power module: the nexus-style-fc main board's POWER and USB blocks (../../nexus-style-fc/tools/design.py,
groups "POWER" and "USB") on their own board.

Parts, values, LCSC codes, nets and reference designators come straight from design.py, so the module
always matches the main board; only the grouping, the placement and the two headers are added here.
The schematic drawing is in gen_power_schematic.py, the PCB in build_power_module.py.

  J1 in  : VX, GND
  J6     : USB-C (VBUS through the F1 PTC, Rd 5.1k on CC, USBLC6 ESD)
  J2 out : 5V, GND, VSYS, 3V3, 3V3_DSM, VX_SENSE, 5V_SENSE, GND, USB_DM, USB_DP

Placement: ("xy", x, y, rot, side) or ("near", ref, pad, side), top-view mm from the PCB top-left corner.
All parts sit on the top side (single-sided JLC assembly).
"""
import copy
import os
import sys

# the main board's design and generators live in the sibling nexus-style-fc project
NEXUS_TOOLS = os.path.normpath(os.path.join(os.path.dirname(os.path.abspath(__file__)), "..", "..", "nexus-style-fc", "tools"))
sys.path.insert(1, NEXUS_TOOLS)

import design  # noqa: E402

TITLE = "Nexus-style FBL - power module"
REV = "0.1"
W, L = 28.0, 25.0                      # board outline, mm

GROUP_TITLES = {
    "BUCK5": "5V BUCK  TPS62130 3 A, 2.5 MHz  + VX input TVS",
    "MUX": "5V PRIORITY MUX  TPS2116: buck (VIN1) first, USB VBUS (VIN2) second",
    "BUCK3": "3V3 MCU BUCK  TPS629210 1 A, fed from VSYS (VX or VBUS through Schottky OR)  + DSM 3V3 port fuse",
    "SENSE": "ADC SENSE  VX x0.161 (vbec_divider 160) | 5V x0.323 (vbus_divider 320)",
    "USB": "USB-C  (VBUS PTC, Rd 5.1k on CC, USBLC6 ESD on D+ / D-)",
}

# main-board ref -> module sub-block
BLOCK = {"D4": "BUCK5", "U5": "BUCK5", "L1": "BUCK5", "U9": "MUX", "D5": "BUCK3", "D6": "BUCK3",
         "U14": "BUCK3", "L2": "BUCK3", "F2": "BUCK3", "J6": "USB", "F1": "USB", "U7": "USB"}
NOTE_BLOCK = {"buck in, 25 V (TI typical: 10 uF)": "BUCK5", "AVIN": "BUCK5", "soft start": "BUCK5",
              "buck out (TI typical: 22 uF)": "BUCK5", "Vout = 0.8 x (1 + 120/22) = 5.16 V": "BUCK5",
              "switch-over at 1.0 V x 127/27 = 4.7 V": "MUX", "VIN2": "MUX", "5 V bus bulk": "MUX",
              "S-CONF #9: VSET, auto PFM, discharge": "BUCK3", "buck in, 25 V": "BUCK3",
              "buck out (TI typical 22 uF), 10 V": "BUCK3", "UFP Rd": "USB"}


def _block(p):
    if p["ref"] in BLOCK:
        return BLOCK[p["ref"]]
    if p["note"] in NOTE_BLOCK:
        return NOTE_BLOCK[p["note"]]
    nets = set(p["pins"].values())
    if nets & {"VX_SENSE", "5V_SENSE"}:
        return "SENSE"
    if nets & {"FB_5V"}:
        return "BUCK5"
    if nets & {"PR1"}:
        return "MUX"
    raise SystemExit(f"design_power: no block for {p['ref']} ({p['note']})")


PARTS = []
for _p in sorted((p for p in design.PARTS if p["group"] in ("POWER", "USB")),
                 key=lambda p: ("JUDLFRC".index(p["ref"][0]), int(p["ref"][1:]))):
    q = copy.deepcopy(_p)
    q["group"] = _block(q)
    PARTS.append(q)
_by_ref = {p["ref"]: p for p in PARTS}

PARTS.insert(0, dict(ref="J1", sym="Connector_Generic:Conn_01x02", value="PWR IN",
                     fp="Connector_PinHeader_2.54mm:PinHeader_1x02_P2.54mm_Vertical", lcsc="",
                     pins={"1": "VX", "2": "GND"}, place=None, group="IO",
                     note="input: VX (BEC / servo bus)"))
PARTS.insert(1, dict(ref="J2", sym="Connector_Generic:Conn_01x10", value="PWR OUT",
                     fp="Connector_PinHeader_2.54mm:PinHeader_1x10_P2.54mm_Vertical", lcsc="",
                     pins={"1": "5V", "2": "GND", "3": "VSYS", "4": "3V3", "5": "3V3_DSM", "6": "VX_SENSE",
                           "7": "5V_SENSE", "8": "GND", "9": "USB_DM", "10": "USB_DP"}, place=None, group="IO",
                     note="outputs to the main board; sense lines go to MCU PC0 (VX) / PC1 (5V), USB to PA11 / PA12"))

# ---------------------------------------------------------------- placement (top side only)
# VX header, its TVS and the USB-C socket along the top edge, output header along the bottom edge (pins run
# left to right, pin names on the silkscreen between header and parts); 5V buck on the left, mux in the
# middle, USB ESD and 3V3 buck on the right
LAYOUT = {
    "D4": ("xy", 4.0, 1.8, 180, "F"),        # TVS right beside the VX pin
    "J1": ("xy", 8.6, 1.6, 90, "F"),         # pins left to right: VX GND
    "F1": ("xy", 14.2, 3.2, 90, "F"),        # VBUS fuse between the socket and the rest
    "J6": ("xy", 21.4, 3.4, 0, "F"),         # USB-C, top entry
    "U7": ("xy", 21.4, 8.6, 90, "F"),        # ESD right under the socket's data pins
    "L1": ("xy", 2.6, 11.4, 90, "F"),        # SW pad at the bottom, 5V_BUCK pad at the top
    "U5": ("xy", 7.3, 11.0, 0, "F"),         # SW pins face L1, VIN pins face the input caps
    "D5": ("xy", 11.6, 7.6, 90, "F"),        # VX -> VSYS
    "D6": ("xy", 14.2, 7.6, 90, "F"),        # VBUS -> VSYS, under F1
    "U9": ("xy", 14.4, 14.4, 0, "F"),
    "U14": ("xy", 22.4, 13.2, 0, "F"),
    "L2": ("xy", 21.7, 16.4, 0, "F"),        # SW pad under U14 pin 4
    "F2": ("xy", 15.4, 18.6, 0, "F"),        # above the 3V3 / DSM pins of J2
    "J2": ("xy", 2.57, 23.4, 90, "F"),       # pins left to right: 5V GND VSYS 3V3 DSM VX_S 5V_S GND D- D+
}
for _p in PARTS:
    _p["place"] = LAYOUT.get(_p["ref"])
    if _p["place"]:
        continue
    # passives: next to the pin of their block's IC that they serve (pins in priority order)
    ic, pads = {"BUCK5": ("U5", ("5", "9", "10", "14")), "MUX": ("U9", ("4", "6", "2")),
                "BUCK3": ("U14", ("8", "6", "3")), "SENSE": ("J2", ("6", "7")),
                "USB": ("J6", ("A5", "B5"))}[_p["group"]]
    anchor = _by_ref.get(ic) or next(p for p in PARTS if p["ref"] == ic)
    hit = [pad for pad in pads if anchor["pins"][pad] in set(_p["pins"].values())]
    if not hit:
        raise SystemExit(f"design_power: no placement for {_p['ref']}")
    _p["place"] = ("near", ic, hit[0], "F")



def nets():
    out = {}
    for p in PARTS:
        for pad, net in p["pins"].items():
            if net:
                out.setdefault(net, []).append((p["ref"], pad))
    return out


if __name__ == "__main__":
    n = nets()
    print(len(PARTS), "parts,", len(n), "nets")
    for p in PARTS:
        print(f"  {p['ref']:4} {p['value']:14} {p['group']:6} {p['place']}  {p['note']}")
    for name, conns in sorted(n.items()):
        if len(conns) < 2:
            print("single-pin net:", name, conns)
